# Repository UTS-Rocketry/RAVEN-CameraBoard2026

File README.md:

# Raven - CameraBoard – UTS Rocketry Avionics

## Version 1.0
High-reliability camera control and downlink board built around the **STM32F405RGT6**, designed for UTS Rocketry’s flight avionics stack.  
The board provides **camera power switching**, **camera UART control**, **video downlink support**, and **CAN-based communication** with the central avionics system.

---

## Project Overview
The CameraBoard is a custom PCB designed to interface action cameras with the UTS Rocketry avionics system.  
It provides:

- **Reliable power delivery** to the camera through a load-switch architecture  
- **UART-based camera control** (start/stop recording, mode switching, etc.)  
- **Video downlink support** (placeholder until RF/video module is finalised)  
- **CAN Bus** connectivity for inter-module communication  
- **Debug UART** and activity LEDs  
- **5V → 3.3V power tree** and full onboard decoupling network  

Built around the **STM32F405RGT6**, chosen for performance, CAN support, and strong STM32 ecosystem compatibility.

---

## Key Features
- **STM32F405RGT6 MCU**
- **Camera Power Switching**
  - Load switch controlled via GPIO  
  - Local decoupling + bulk capacitance
- **Camera Control (UART)**
  - Compatible with RunCam-style UART protocols
- **CAN Bus Interface**
  - TX/RX routed to CAN transceiver  
  - Interfaces with the main flight computer
- **Video Downlink Support**
  - Reserved connector footprint  
  - Pins allocated for future video transmitter module
- **Debug Interface**
  - UART for logging  
  - Status, power, and activity LEDs
- **Power Topology**
  - Headers for 5V buck converters  
  - 3.3V rail for MCU and logic  
  - Full decoupling network following ST guidelines

## Contributors
Reed Basangan — Software Lead, UTS Rocketry
UTS Rocketry Avionics Team

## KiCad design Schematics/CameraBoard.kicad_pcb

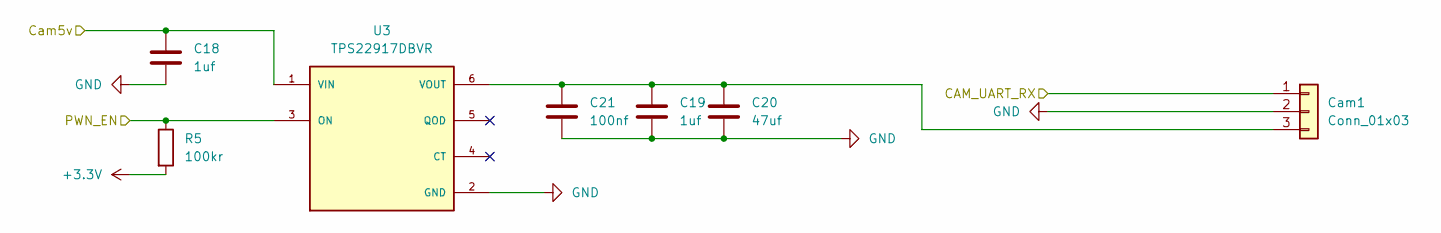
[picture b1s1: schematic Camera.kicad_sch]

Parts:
C18, C19: 1uf; C_0805_2012Metric_Pad1.18x1.45mm_HandSolder; LCSC C28323
C20: 47uf; C_0805_2012Metric_Pad1.18x1.45mm_HandSolder; LCSC C16780
C21: 100nf; C_0805_2012Metric_Pad1.18x1.45mm_HandSolder; LCSC C49678
Cam1: Conn_01x03; JST_PH_B3B-PH-K_1x03_P2.00mm_Vertical; LCSC C131339
R5: 100kr; R_0805_2012Metric_Pad1.20x1.40mm_HandSolder; LCSC C149504
U3: TPS22917DBVR; SOT95P280X145-6N; PARTREV B; LCSC C2681320

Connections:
+3.3V: R5.2; also elsewhere on the board
+5V: C18.1, U3.1 (VIN); also elsewhere on the board
/Camera_center/CAM_UART_RX: Cam1.1; also elsewhere on the board
/Camera_left/<NO NET>: C19.1, C20.1, C21.1, Cam1.3, U3.6 (VOUT)
/Camera_left/PWN_EN: R5.1, U3.3 (ON); also elsewhere on the board
GND: C18.2, C19.2, C20.2, C21.2, Cam1.2, U3.2 (GND); also elsewhere on the board

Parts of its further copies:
C23, C24, C27, C28: 1uf; C_0805_2012Metric_Pad1.18x1.45mm_HandSolder; LCSC C28323
C25, C29: 47uf; C_0805_2012Metric_Pad1.18x1.45mm_HandSolder; LCSC C16780
C26, C30: 100nf; C_0805_2012Metric_Pad1.18x1.45mm_HandSolder; LCSC C49678
Cam2, Cam3: Conn_01x03; JST_PH_B3B-PH-K_1x03_P2.00mm_Vertical; LCSC C131339
R9, R10: 100kr; R_0805_2012Metric_Pad1.20x1.40mm_HandSolder; LCSC C149504
U5, U6: TPS22917DBVR; SOT95P280X145-6N; PARTREV B; LCSC C2681320

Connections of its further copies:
+3.3V: R9.2, R10.2; also elsewhere on the board
+5V: C23.1, C27.1, U5.1 (VIN), U6.1 (VIN); also elsewhere on the board
/Camera_center/<NO NET>: C28.1, C29.1, C30.1, Cam3.3, U6.6 (VOUT)
/Camera_center/CAM_UART_RX: Cam2.1, Cam3.1; also elsewhere on the board
/Camera_center/PWN_EN: R10.1, U6.3 (ON); also elsewhere on the board
/Camera_right/<NO NET>: C24.1, C25.1, C26.1, Cam2.3, U5.6 (VOUT)
/Camera_right/PWN_EN: R9.1, U5.3 (ON); also elsewhere on the board
GND: C23.2, C24.2, C25.2, C26.2, C27.2, C28.2, C29.2, C30.2, Cam2.2, Cam3.2, U5.2 (GND), U6.2 (GND); also elsewhere on the board

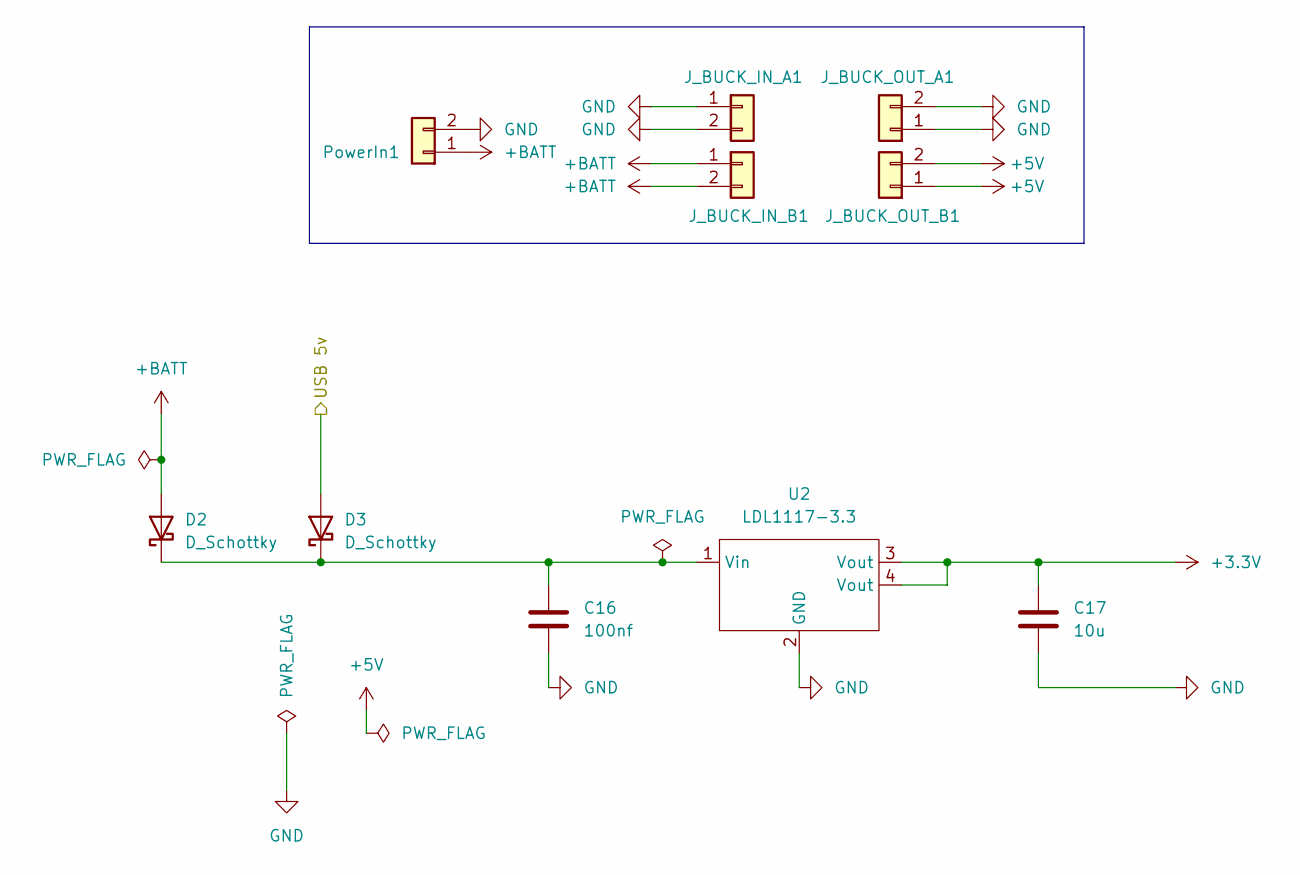
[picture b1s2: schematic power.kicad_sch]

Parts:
C16: 100nf; C_0805_2012Metric_Pad1.18x1.45mm_HandSolder; LCSC Part C28323
C17: 10u; C_0805_2012Metric_Pad1.18x1.45mm_HandSolder; LCSC Part C98192
D2, D3: D_Schottky; D_2114_3652Metric; LCSC C113936
J_BUCK_IN_A1: PinSocket_1x02_P2.54mm_Horizontal
J_BUCK_IN_B1: PinSocket_1x02_P2.54mm_Horizontal
J_BUCK_OUT_A1: PinSocket_1x02_P2.54mm_Horizontal
J_BUCK_OUT_B1: PinSocket_1x02_P2.54mm_Horizontal
PowerIn1: 2 pin Molex; MOLEX_26013114; LCSC C17644051
U2: LDL1117-3.3; SOT230P700X180-4N; LCSC C435835

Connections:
+3.3V: C17.1, U2.3 (Vout), U2.4 (Vout); also elsewhere on the board
+5V: J_BUCK_OUT_B1.1, J_BUCK_OUT_B1.2; also elsewhere on the board
+BATT: D2.2 (A), J_BUCK_IN_B1.1, J_BUCK_IN_B1.2, PowerIn1.1
/MCU/VBUS: D3.2 (A); also elsewhere on the board
GND: C16.2, C17.2, J_BUCK_IN_A1.1, J_BUCK_IN_A1.2, J_BUCK_OUT_A1.1, J_BUCK_OUT_A1.2, PowerIn1.2, U2.2 (GND); also elsewhere on the board
unnamed: C16.1, D2.1 (K), D3.1 (K), U2.1 (Vin)

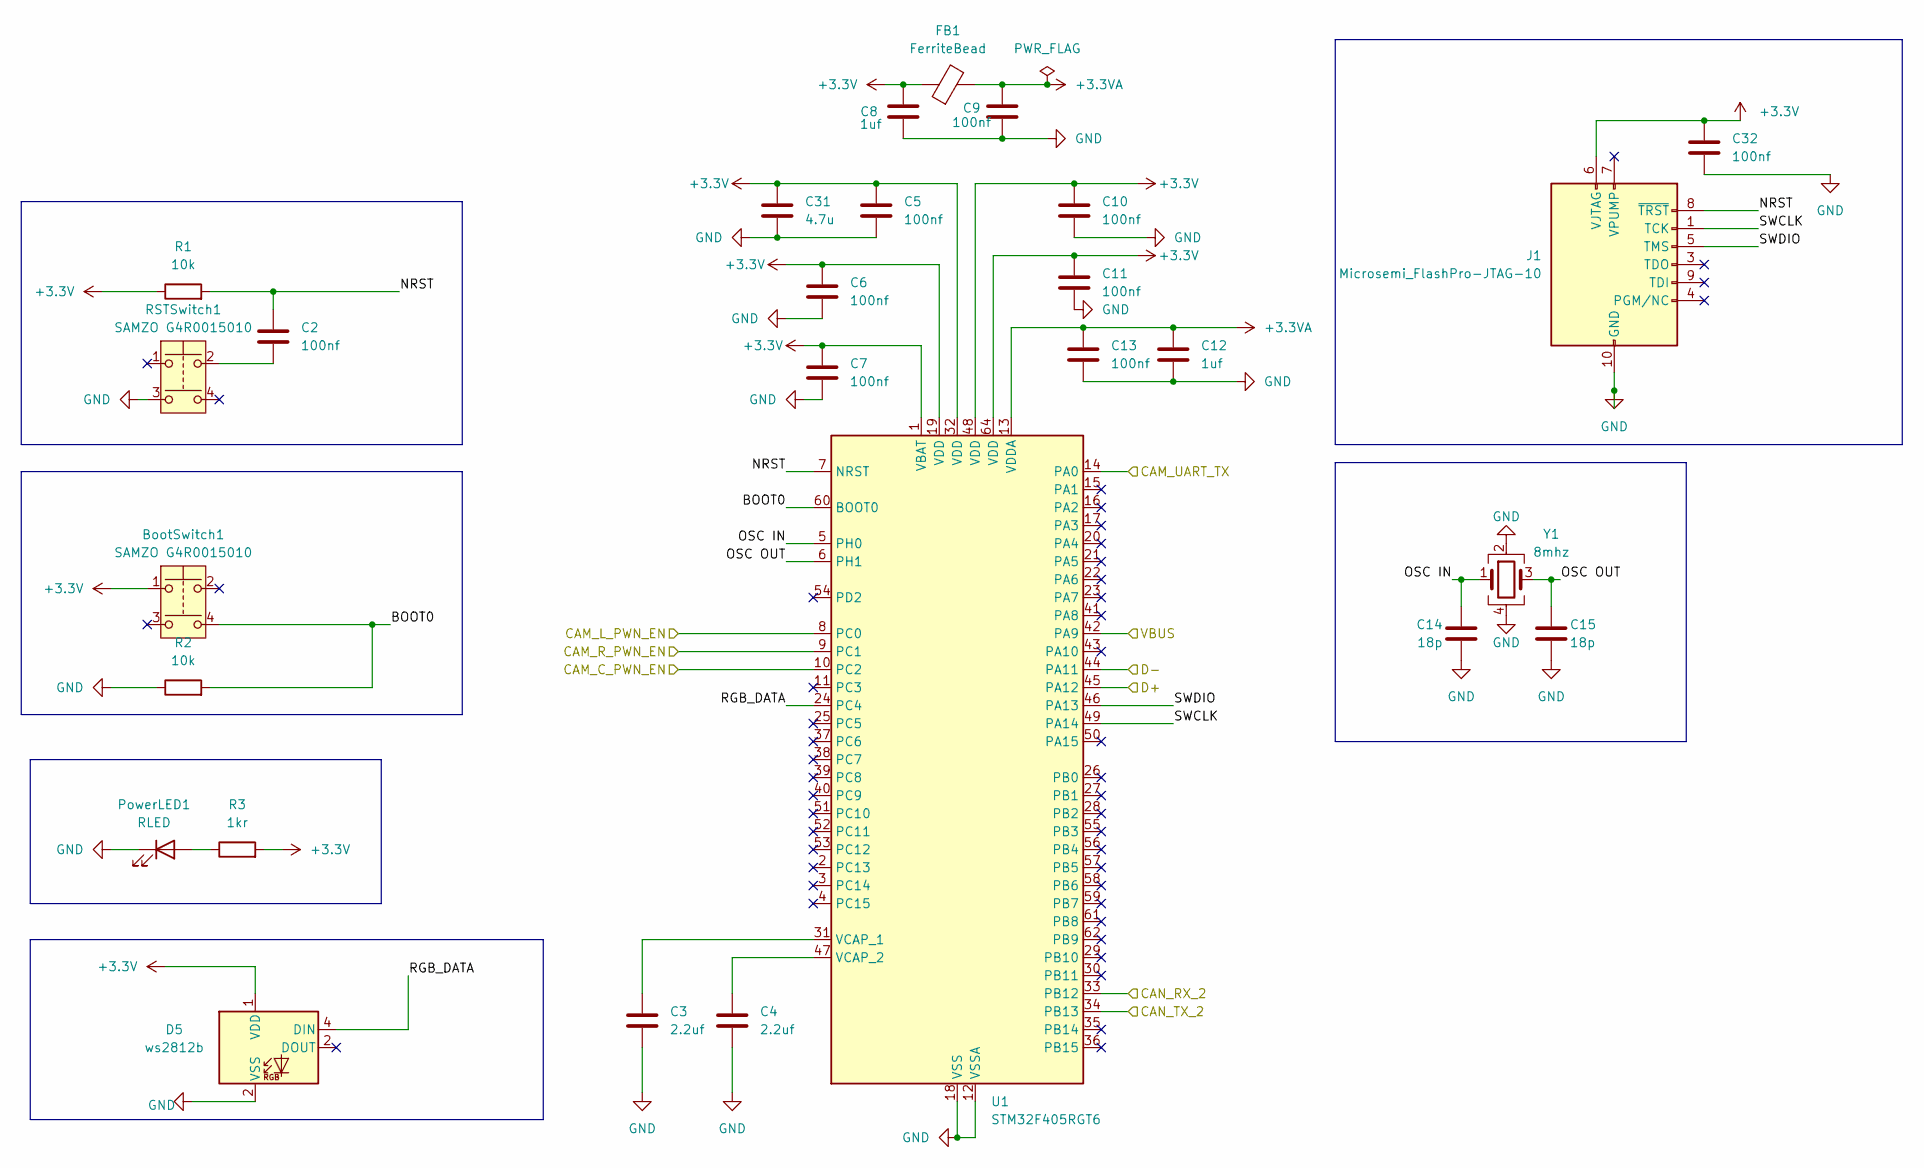
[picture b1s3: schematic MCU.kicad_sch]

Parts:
BootSwitch1: SAMZO G4R0015010; LCSC C49393646
C2, C5, C6, C7, C9, C10, C11, C13, C32: 100nf; C_0805_2012Metric_Pad1.18x1.45mm_HandSolder; LCSC C49678
C3, C4: 2.2uf; C_0805_2012Metric_Pad1.18x1.45mm_HandSolder; LCSC C377773
C8, C12: 1uf; C_0805_2012Metric_Pad1.18x1.45mm_HandSolder; LCSC C28323
C14, C15: 18p; C_0603_1608Metric_Pad1.08x0.95mm_HandSolder; LCSC Part C1647
C31: 4.7u; C_0805_2012Metric_Pad1.18x1.45mm_HandSolder; LCSC C1779
D5: ws2812b; LED_WS2812B_PLCC4_5.0x5.0mm_P3.2mm; LCSC C114586
FB1: FerriteBead; R_0805_2012Metric_Pad1.20x1.40mm_HandSolder; LCSC C85840
J1: Microsemi_FlashPro-JTAG-10; PinHeader_2x05_P1.27mm_Vertical; LCSC C22438120
PowerLED1: RLED; LED_0603_1608Metric_Pad1.05x0.95mm_HandSolder; LCSC C965799
R1, R2: 10k; R_0805_2012Metric_Pad1.20x1.40mm_HandSolder; LCSC C84376
R3: 1kr; R_0805_2012Metric_Pad1.20x1.40mm_HandSolder; LCSC C17513
RSTSwitch1: SAMZO G4R0015010; LCSC C49393646
U1: STM32F405RGT6; LQFP-64_10x10mm_P0.5mm; LCSC C15742
Y1: 8mhz; Crystal_SMD_3225-4Pin_3.2x2.5mm_HandSoldering; LCSC Part C19723344

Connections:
+3.3V: BootSwitch1.1, C5.1, C6.1, C7.1, C8.2, C10.1, C11.1, C31.1, C32.1, D5.1 (VDD), FB1.1, J1.6 (VJTAG), R1.1, R3.2, U1.1 (VBAT), U1.19 (VDD), U1.32 (VDD), U1.48 (VDD), U1.64 (VDD); also elsewhere on the board
+3.3VA: C9.2, C12.1, C13.1, FB1.2, U1.13 (VDDA)
/Camera_center/CAM_UART_RX: U1.14 (PA0); also elsewhere on the board
/Camera_center/PWN_EN: U1.10 (PC2); also elsewhere on the board
/Camera_left/PWN_EN: U1.8 (PC0); also elsewhere on the board
/Camera_right/PWN_EN: U1.9 (PC1); also elsewhere on the board
/Can_transceiver/CAN_RX_2: U1.34 (PB13); also elsewhere on the board
/Can_transceiver/CAN_TX_2: U1.33 (PB12); also elsewhere on the board
/MCU/BOOT0: BootSwitch1.4, R2.2, U1.60 (BOOT0)
/MCU/D+: U1.45 (PA12); also elsewhere on the board
/MCU/D-: U1.44 (PA11); also elsewhere on the board
/MCU/NRST: C2.1, J1.8 (~TRST), R1.2, U1.7 (NRST)
/MCU/OSC IN: C14.1, U1.5 (PH0), Y1.1
/MCU/OSC OUT: C15.1, U1.6 (PH1), Y1.3
/MCU/RGB_DATA: D5.4 (DIN), U1.24 (PC4)
/MCU/SWCLK: J1.1 (TCK), U1.49 (PA14)
/MCU/SWDIO: J1.5 (TMS), U1.46 (PA13)
/MCU/VBUS: U1.42 (PA9); also elsewhere on the board
GND: C3.2, C4.2, C5.2, C6.2, C7.2, C8.1, C9.1, C10.2, C11.2, C12.2, C13.2, C14.2, C15.2, C31.2, C32.2, D5.2 (VSS), J1.2 (GND), J1.10 (GND), PowerLED1.1 (K), R2.1, RSTSwitch1.3, U1.12 (VSSA), U1.18 (VSS), U1.63 (VSS), Y1.2, Y1.4; also elsewhere on the board
unnamed: C2.2, RSTSwitch1.2
unnamed: PowerLED1.2 (A), R3.1
unnamed: C3.1, U1.31 (VCAP_1)
unnamed: C4.1, U1.47 (VCAP_2)

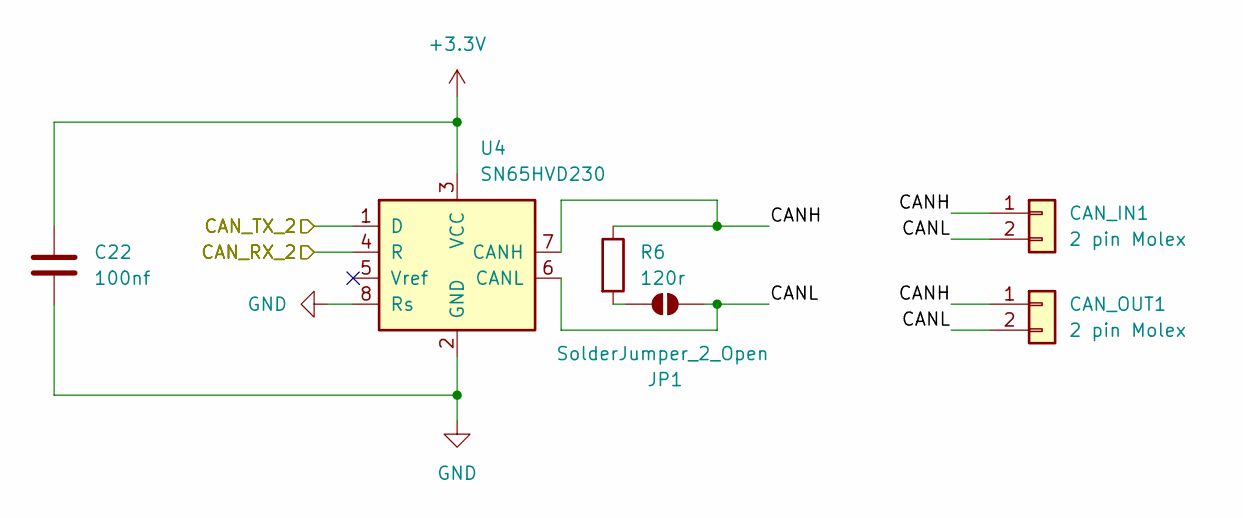
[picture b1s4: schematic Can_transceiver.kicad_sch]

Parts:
C22: 100nf; C_0805_2012Metric_Pad1.18x1.45mm_HandSolder; lcsc C6565120
CAN_IN1: 2 pin Molex; MOLEX_26013114; LCSC C17644051
CAN_OUT1: 2 pin Molex; MOLEX_26013114; LCSC C17644051
JP1: SolderJumper_2_Open; SolderJumper-2_P1.3mm_Open_TrianglePad1.0x1.5mm
R6: 120r; R_0603_1608Metric; lcsc C4353191
U4: SN65HVD230; SOIC-8_3.9x4.9mm_P1.27mm; lcsc C12084

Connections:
+3.3V: C22.1, U4.3 (VCC); also elsewhere on the board
/Can_transceiver/CANH: CAN_IN1.1, CAN_OUT1.1, R6.1, U4.7 (CANH)
/Can_transceiver/CANL: CAN_IN1.2, CAN_OUT1.2, JP1.2 (B), U4.6 (CANL)
/Can_transceiver/CAN_RX_2: U4.4 (R); also elsewhere on the board
/Can_transceiver/CAN_TX_2: U4.1 (D); also elsewhere on the board
GND: C22.2, U4.2 (GND), U4.8 (Rs); also elsewhere on the board
unnamed: JP1.1 (A), R6.2

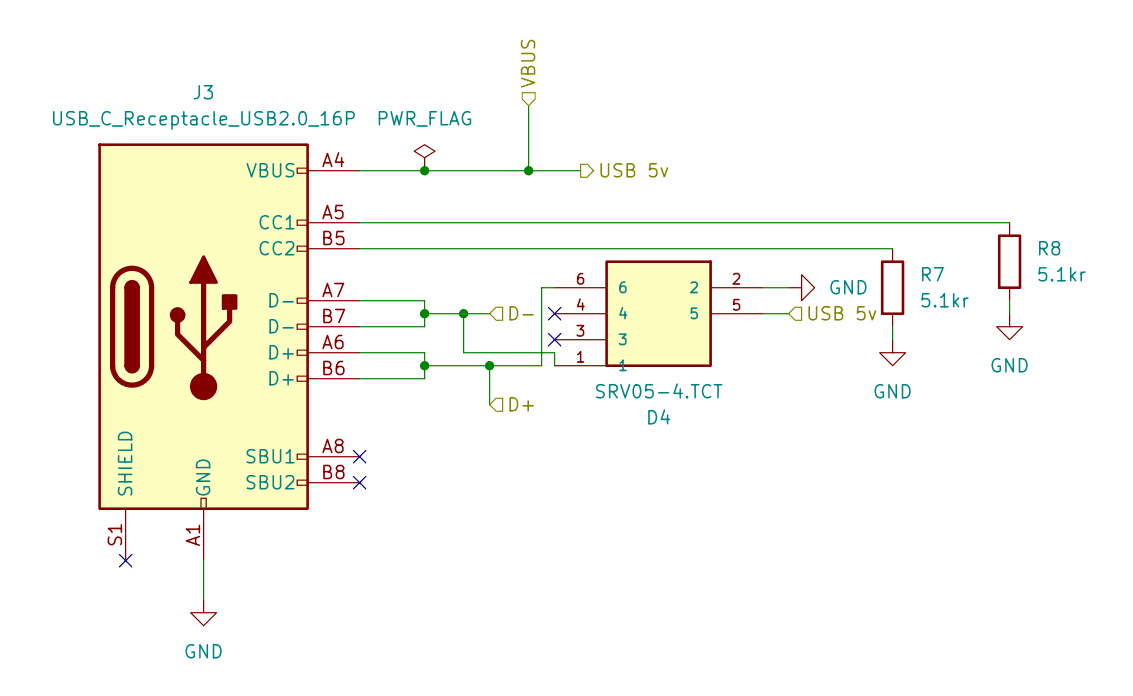
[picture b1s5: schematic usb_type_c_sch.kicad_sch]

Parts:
D4: SRV05-4.TCT; SOT95P280X145-6N; MOUSER_PART_NUMBER 947-SRV05-4.TCT
J3: USB_C_Receptacle_USB2.0_16P; USB_C_Receptacle_HRO_TYPE-C-31-M-12; LCSC C165948
R7, R8: 5.1kr; R_0805_2012Metric_Pad1.20x1.40mm_HandSolder; LCSC C27834

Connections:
/MCU/D+: D4.6, J3.A6 (D+), J3.B6 (D+); also elsewhere on the board
/MCU/D-: D4.1, J3.A7 (D-), J3.B7 (D-); also elsewhere on the board
/MCU/VBUS: D4.5, J3.A4 (VBUS), J3.A9 (VBUS), J3.B4 (VBUS), J3.B9 (VBUS); also elsewhere on the board
GND: D4.2, J3.A1 (GND), J3.A12 (GND), J3.B1 (GND), J3.B12 (GND), R7.2, R8.2; also elsewhere on the board
unnamed: J3.A5 (CC1), R8.1
unnamed: J3.B5 (CC2), R7.1

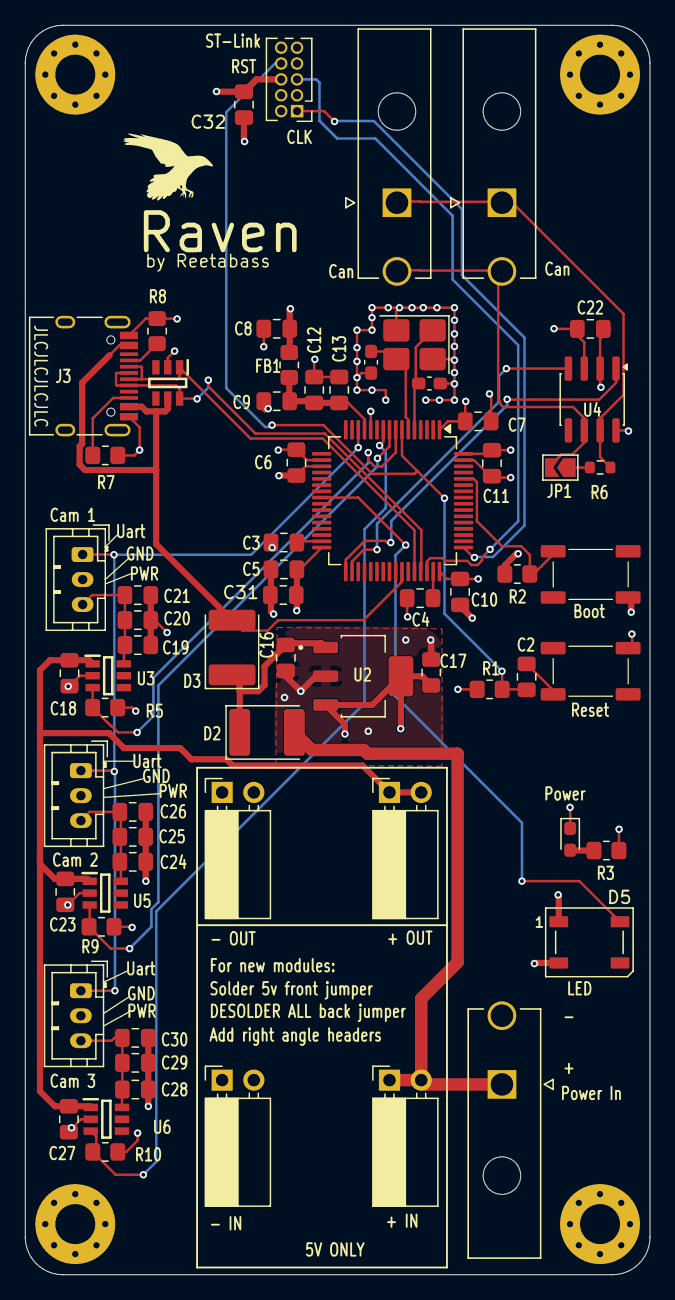
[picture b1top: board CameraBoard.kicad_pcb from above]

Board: 4 copper layers, 50.0 x 100.0 mm, 68 parts (0 on the bottom side), 34 nets.

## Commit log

2026-03-01 fixing remote
2026-03-02 fixed schematic and named ready for bom to order
2026-03-02 output files completed quote obtained
2026-03-03 fixed buck converter routing
2026-03-04 final output files
2026-03-16 dfm complete sent for order
2026-03-23 fixed can tranciver issues and updated to KiCad 10.0
2026-03-24 updated stlink connector
2026-03-25 updating schematic for final order
